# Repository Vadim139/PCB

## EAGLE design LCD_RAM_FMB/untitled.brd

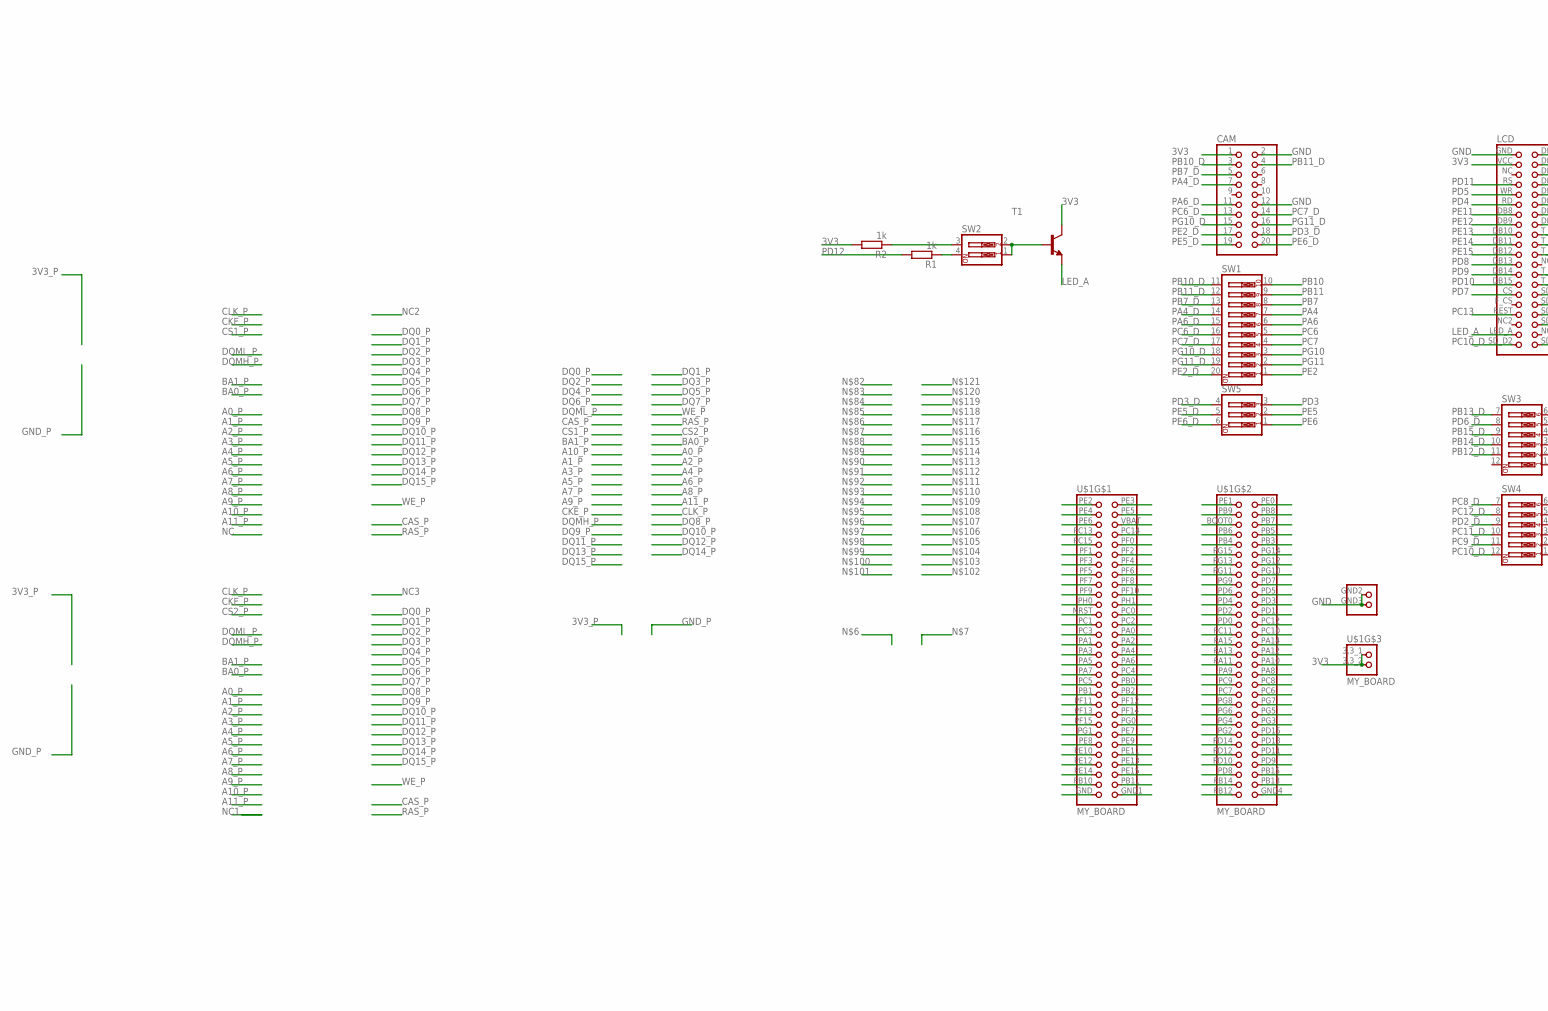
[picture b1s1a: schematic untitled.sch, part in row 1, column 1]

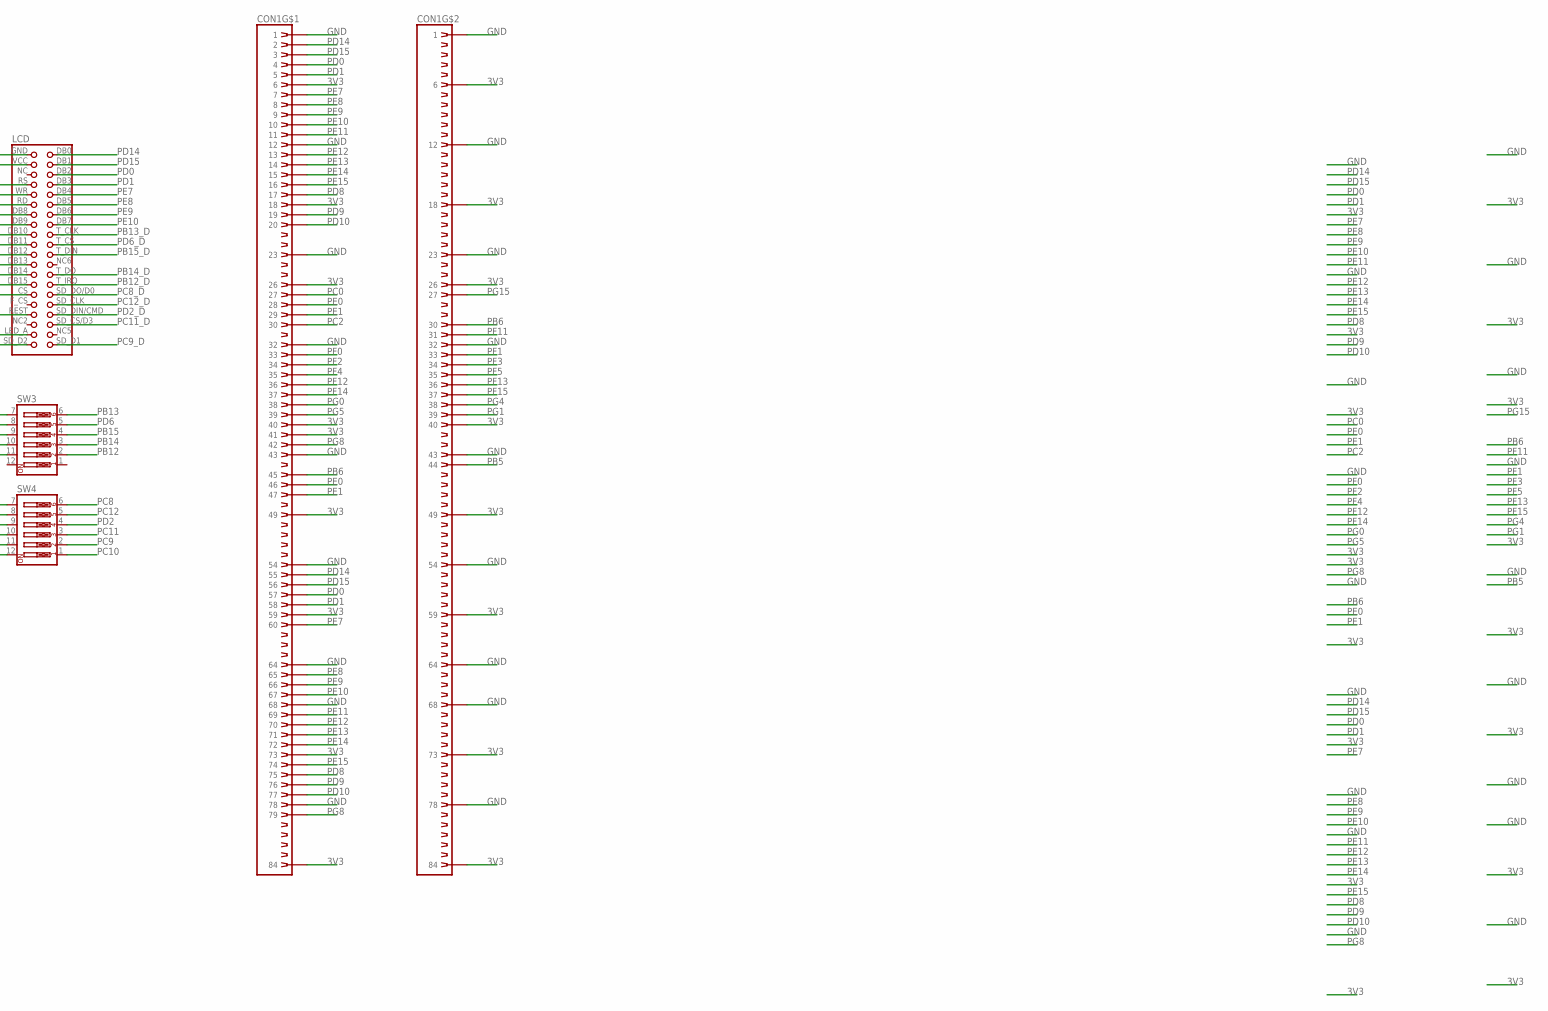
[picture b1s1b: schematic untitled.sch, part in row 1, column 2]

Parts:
CAM: PINHD-2X10; 2X10
CON1: DIMM168; 390052-4
LCD: LCD320QVBLCD320QVB; 2X20
R1, R2: 1k; 0204/5
SW1: SW_DIP-10; EDG-10
SW2: SW_DIP-2; EDG-02
SW3, SW4: SW_DIP-6; EDG-06
SW5: SW_DIP-3; EDG-03
T1: BC337-NPN-TO92-CBE; TO92-CBE
U$1: MY_BOARD

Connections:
3V3: CAM.1, CON1.6, CON1.18, CON1.26, CON1.40, CON1.41, CON1.49, CON1.59, CON1.73, CON1.84, CON1.90 (6), CON1.102 (18), CON1.110 (26), CON1.124 (40), CON1.133 (49), CON1.143 (59), CON1.157 (73), CON1.168 (84), LCD.VCC (3), R2.2, T1.C, U$1.3,3_1 (1), U$1.3,3_2 (2)
BOOT0: U$1.BOOT0 (5)
GND: CAM.2, CAM.12, CON1.1, CON1.12, CON1.23, CON1.32, CON1.43, CON1.54, CON1.64, CON1.68, CON1.78, CON1.85 (1), CON1.96 (12), CON1.107 (23), CON1.116 (32), CON1.127 (43), CON1.138 (54), CON1.148 (64), CON1.152 (68), CON1.162 (78), LCD.GND (1), U$1.GND (59), U$1.GND1 (60), U$1.GND2 (3), U$1.GND3 (4), U$1.GND4 (60)
LED_A: LCD.LED_A (37), T1.E
unnamed: SW2.1, SW2.2, T1.B
unnamed: R2.1, SW2.3
unnamed: R1.1, SW2.4
NRST: U$1.NRST (23)
PA0: U$1.PA0 (28)
PA1: U$1.PA1 (29)
PA2: U$1.PA2 (30)
PA3: U$1.PA3 (31)
PA4: SW1.7, U$1.PA4 (32)
PA4_D: CAM.7, SW1.14
PA5: U$1.PA5 (33)
PA6: SW1.6, U$1.PA6 (34)
PA6_D: CAM.11, SW1.15
PA7: U$1.PA7 (35)
PA8: U$1.PA8 (36)
PA9: U$1.PA9 (35)
PA10: U$1.PA10 (34)
PA11: U$1.PA11 (33)
PA12: U$1.PA12 (32)
PA13: U$1.PA13 (31)
PA14: U$1.PA14 (30)
PA15: U$1.PA15 (29)
PB0: U$1.PB0 (38)
PB1: U$1.PB1 (39)
PB2: U$1.PB2 (40)
PB3: U$1.PB3 (10)
PB4: U$1.PB4 (9)
PB5: CON1.128 (44), U$1.PB5 (8)
PB6: CON1.45, CON1.114 (30), U$1.PB6 (7)
PB7: SW1.8, U$1.PB7 (6)
PB7_D: CAM.5, SW1.13
PB8: U$1.PB8 (4)
PB9: U$1.PB9 (3)
PB10: SW1.10, U$1.PB10 (57)
PB10_D: CAM.3, SW1.11
PB11: SW1.9, U$1.PB11 (58)
PB11_D: CAM.4, SW1.12
PB12: SW3.2, U$1.PB12 (59)
PB12_D: LCD.T_IRQ (28), SW3.11
PB13: SW3.6, U$1.PB13 (58)
PB13_D: LCD.T_CLK (18), SW3.7
PB14: SW3.3, U$1.PB14 (57)
PB14_D: LCD.T_DO (26), SW3.10
PB15: SW3.4, U$1.PB15 (56)
PB15_D: LCD.T_DIN (22), SW3.9
PC0: CON1.27, U$1.PC0 (24)
PC1: U$1.PC1 (25)
PC2: CON1.30, U$1.PC2 (26)
PC3: U$1.PC3 (27)
PC4: U$1.PC4 (36)
PC5: U$1.PC5 (37)
PC6: SW1.5, U$1.PC6 (40)
PC6_D: CAM.13, SW1.16
PC7: SW1.4, U$1.PC7 (39)
PC7_D: CAM.14, SW1.17
PC8: SW4.6, U$1.PC8 (38)
PC8_D: LCD.SD_DO/D0 (30), SW4.7
PC9: SW4.2, U$1.PC9 (37)
PC9_D: LCD.SD_D1 (40), SW4.11
PC10: SW4.1, U$1.PC10 (28)
PC10_D: LCD.SD_D2 (39), SW4.12
PC11: SW4.3, U$1.PC11 (27)
PC11_D: LCD.SD_CS/D3 (36), SW4.10
PC12: SW4.5, U$1.PC12 (26)
PC12_D: LCD.SD_CLK (32), SW4.8
PC13: LCD.REST (33), U$1.PC13 (7)
PC14: U$1.PC14 (8)
PC15: U$1.PC15 (9)
PD0: CON1.4, CON1.57, LCD.DB2 (6), U$1.PD0 (25)
PD1: CON1.5, CON1.58, LCD.DB3 (8), U$1.PD1 (24)
PD2: SW4.4, U$1.PD2 (23)
PD2_D: LCD.SD_DIN/CMD (34), SW4.9
PD3: SW5.3, U$1.PD3 (22)
PD3_D: CAM.18, SW5.4
PD4: LCD.RD (11), U$1.PD4 (21)
PD5: LCD.WR (9), U$1.PD5 (20)
PD6: SW3.5, U$1.PD6 (19)
PD6_D: LCD.T_CS (20), SW3.8
PD7: LCD.CS (29), U$1.PD7 (18)
PD8: CON1.17, CON1.75, LCD.DB13 (23), U$1.PD8 (55)
PD9: CON1.19, CON1.76, LCD.DB14 (25), U$1.PD9 (54)
PD10: CON1.20, CON1.77, LCD.DB15 (27), U$1.PD10 (53)
PD11: LCD.RS (7), U$1.PD11 (52)
PD12: R1.2, U$1.PD12 (51)
PD13: U$1.PD13 (50)
PD14: CON1.2, CON1.55, LCD.DB0 (2), U$1.PD14 (49)
PD15: CON1.3, CON1.56, LCD.DB1 (4), U$1.PD15 (48)
PE0: CON1.28, CON1.46, U$1.PE0 (2)
PE1: CON1.29, CON1.47, U$1.PE1 (1)
PE2: SW1.1, U$1.PE2 (1)
PE2_D: CAM.17, SW1.20
PE3: U$1.PE3 (2)
PE4: U$1.PE4 (3)
PE5: SW5.2, U$1.PE5 (4)
PE5_D: CAM.19, SW5.5
PE6: SW5.1, U$1.PE6 (5)
PE6_D: CAM.20, SW5.6
PE7: CON1.7, CON1.60, LCD.DB4 (10), U$1.PE7 (48)
PE8: CON1.8, CON1.65, LCD.DB5 (12), U$1.PE8 (49)
PE9: CON1.9, CON1.66, LCD.DB6 (14), U$1.PE9 (50)
PE10: CON1.10, CON1.67, LCD.DB7 (16), U$1.PE10 (51)
PE11: CON1.11, CON1.69, LCD.DB8 (13), U$1.PE11 (52)
PE12: CON1.13, CON1.70, LCD.DB9 (15), U$1.PE12 (53)
PE13: CON1.14, CON1.71, LCD.DB10 (17), U$1.PE13 (54)
PE14: CON1.15, CON1.72, LCD.DB11 (19), U$1.PE14 (55)
PE15: CON1.16, CON1.74, LCD.DB12 (21), U$1.PE15 (56)
PF0: CON1.33, U$1.PF0 (10)
PF1: CON1.117 (33), U$1.PF1 (11)
PF2: CON1.34, U$1.PF2 (12)
PF3: CON1.118 (34), U$1.PF3 (13)
PF4: CON1.35, U$1.PF4 (14)
PF5: CON1.119 (35), U$1.PF5 (15)
PF6: U$1.PF6 (16)
PF7: U$1.PF7 (17)
PF8: U$1.PF8 (18)
PF9: U$1.PF9 (19)
PF10: U$1.PF10 (20)
PF11: CON1.115 (31), U$1.PF11 (41)
PF12: CON1.36, U$1.PF12 (42)
PF13: CON1.120 (36), U$1.PF13 (43)
PF14: CON1.37, U$1.PF14 (44)
PF15: CON1.121 (37), U$1.PF15 (45)
PG0: CON1.38, U$1.PG0 (46)
PG1: CON1.123 (39), U$1.PG1 (47)
PG2: U$1.PG2 (47)
PG3: U$1.PG3 (46)
PG4: CON1.122 (38), U$1.PG4 (45)
PG5: CON1.39, U$1.PG5 (44)
PG6: U$1.PG6 (43)
PG7: U$1.PG7 (42)
PG8: CON1.42, CON1.79, U$1.PG8 (41)
PG9: U$1.PG9 (17)
PG10: SW1.3, U$1.PG10 (16)
PG10_D: CAM.15, SW1.18
PG11: SW1.2, U$1.PG11 (15)
PG11_D: CAM.16, SW1.19
PG12: U$1.PG12 (14)
PG13: U$1.PG13 (13)
PG14: U$1.PG14 (12)
PG15: CON1.111 (27), U$1.PG15 (11)
PH0: U$1.PH0 (21)
PH1: U$1.PH1 (22)
VBAT: U$1.VBAT (6)

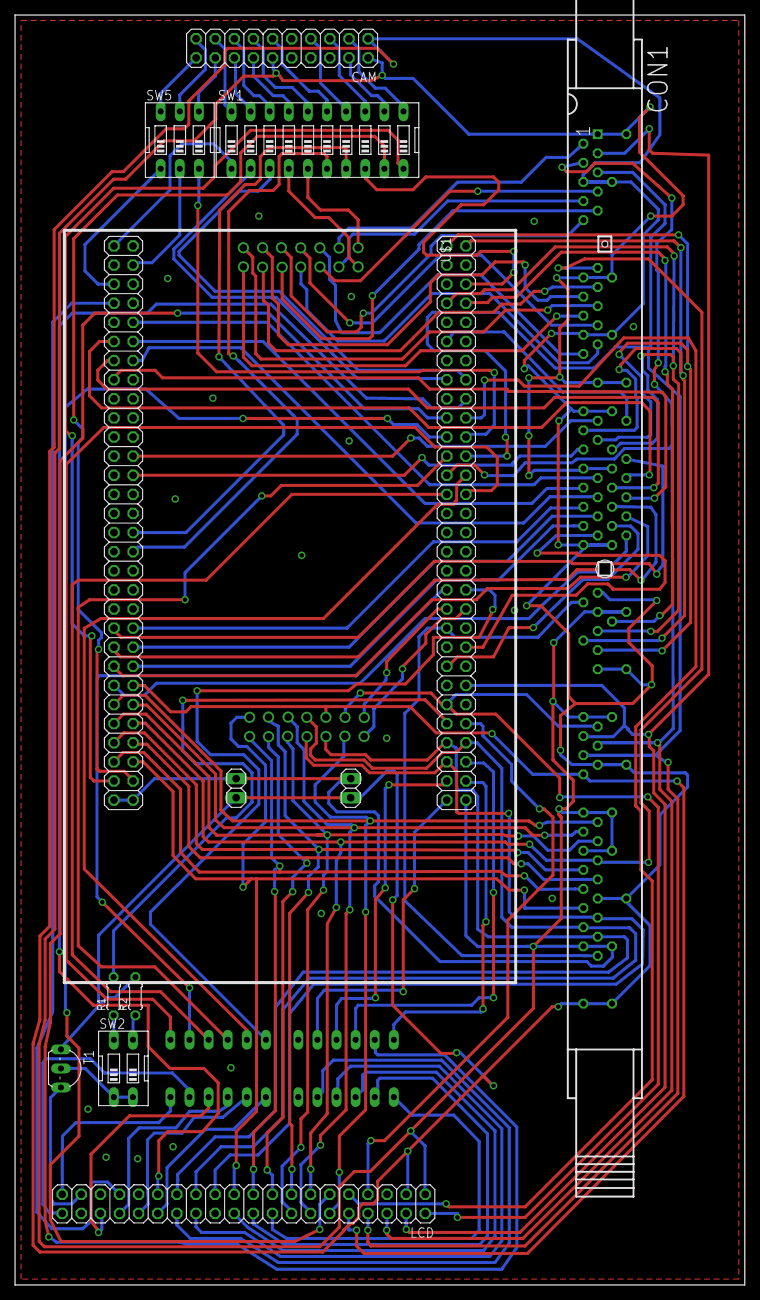
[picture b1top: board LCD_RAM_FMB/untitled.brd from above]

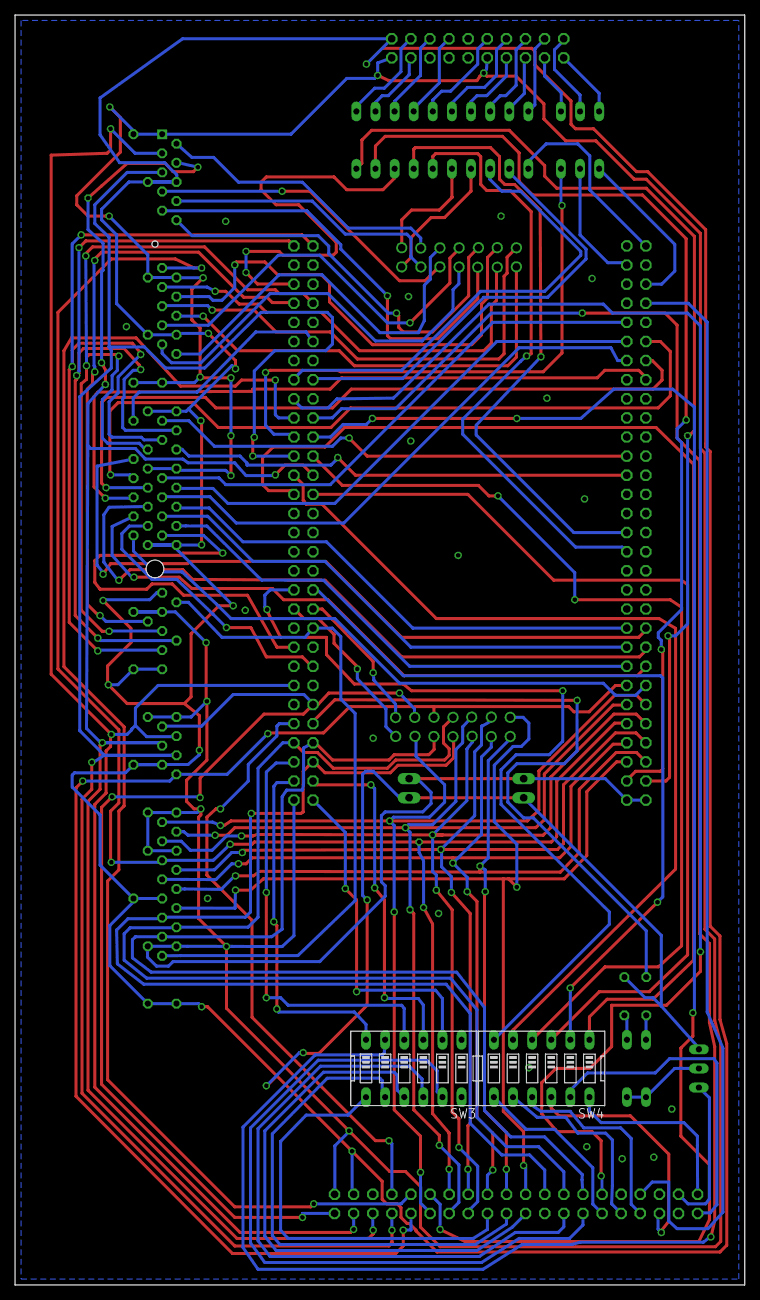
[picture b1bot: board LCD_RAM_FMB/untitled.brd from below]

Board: 2 copper layers, 97.0 x 168.8 mm, 12 parts (2 on the bottom side), 99 nets.

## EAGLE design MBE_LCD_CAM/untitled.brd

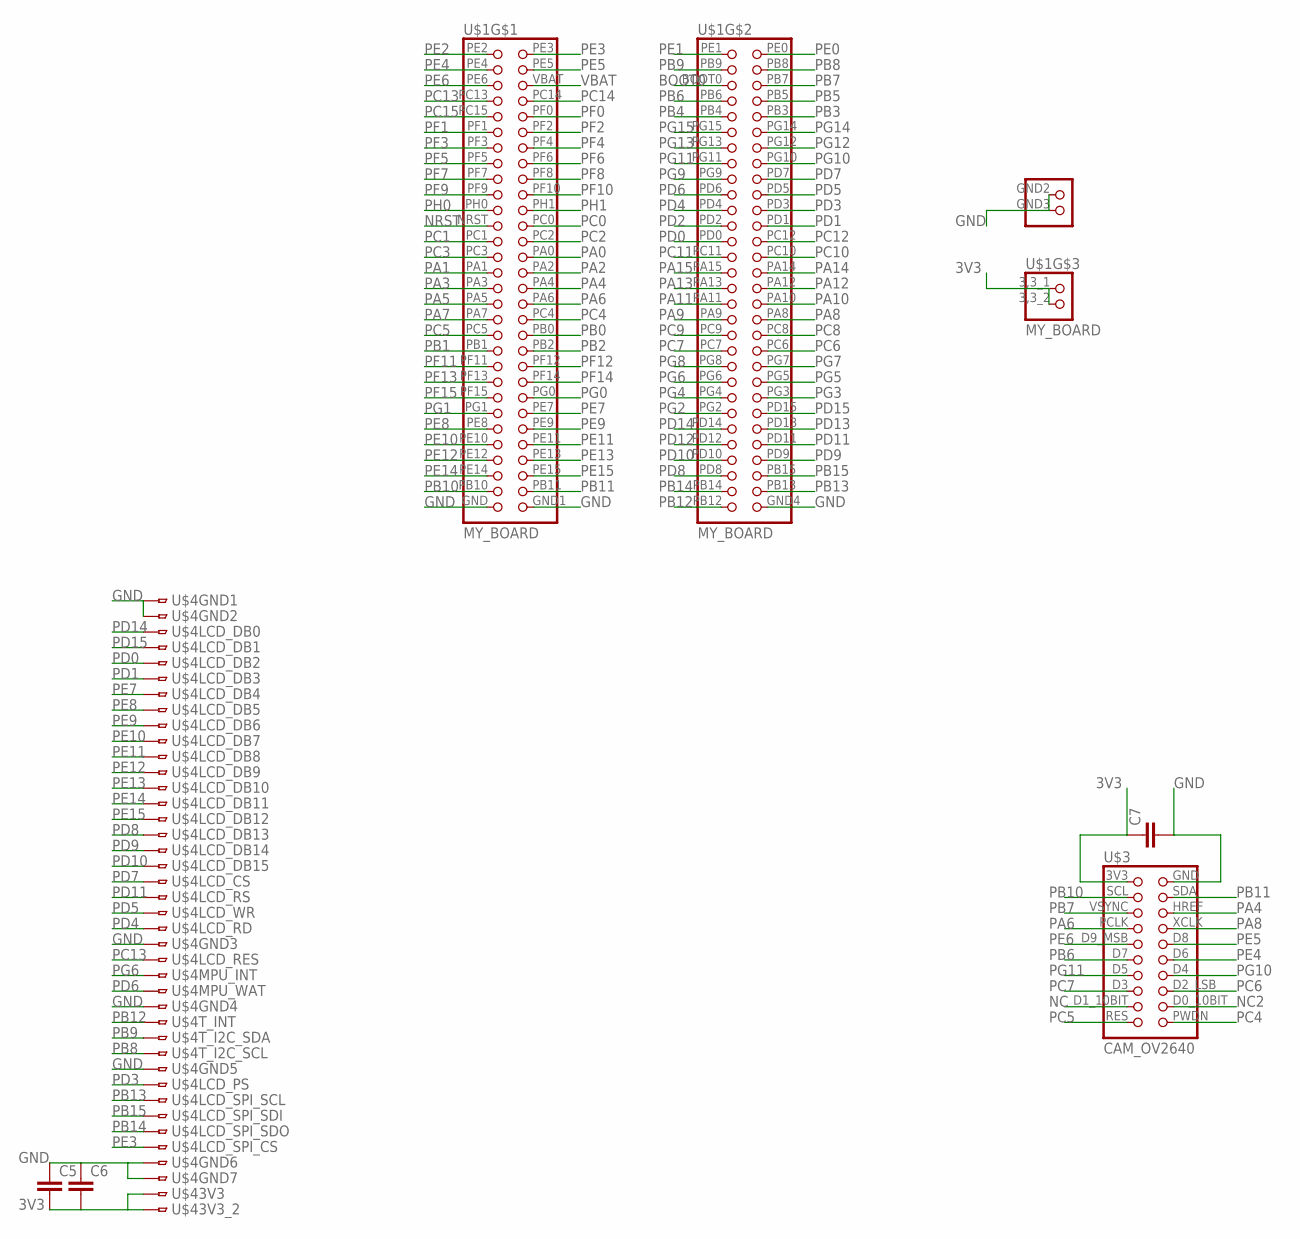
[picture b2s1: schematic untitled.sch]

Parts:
C5, C6, C7: C-EUC1206; C1206
U$1: MY_BOARD
U$3: CAM_OV2640
U$4: LCD800TFT; FH12-40S-0.5SH

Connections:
3V3: C5.2, C6.2, C7.1, U$1.3,3_1 (1), U$1.3,3_2 (2), U$3.3V3, U$4.39, U$4.40
BOOT0: U$1.BOOT0 (5)
GND: C5.1, C6.1, C7.2, U$1.GND (59), U$1.GND1 (60), U$1.GND2 (3), U$1.GND3 (4), U$1.GND4 (60), U$3.GND, U$4.1, U$4.2, U$4.23, U$4.27, U$4.31, U$4.37, U$4.38
NC: U$3.D1_10BIT
NC2: U$3.D0_10BIT
NRST: U$1.NRST (23)
PA0: U$1.PA0 (28)
PA1: U$1.PA1 (29)
PA2: U$1.PA2 (30)
PA3: U$1.PA3 (31)
PA4: U$1.PA4 (32), U$3.HREF
PA5: U$1.PA5 (33)
PA6: U$1.PA6 (34), U$3.PCLK
PA7: U$1.PA7 (35)
PA8: U$1.PA8 (36), U$3.XCLK
PA9: U$1.PA9 (35)
PA10: U$1.PA10 (34)
PA11: U$1.PA11 (33)
PA12: U$1.PA12 (32)
PA13: U$1.PA13 (31)
PA14: U$1.PA14 (30)
PA15: U$1.PA15 (29)
PB0: U$1.PB0 (38)
PB1: U$1.PB1 (39)
PB2: U$1.PB2 (40)
PB3: U$1.PB3 (10)
PB4: U$1.PB4 (9)
PB5: U$1.PB5 (8)
PB6: U$1.PB6 (7), U$3.D7
PB7: U$1.PB7 (6), U$3.VSYNC
PB8: U$1.PB8 (4), U$4.30
PB9: U$1.PB9 (3), U$4.29
PB10: U$1.PB10 (57), U$3.SCL
PB11: U$1.PB11 (58), U$3.SDA
PB12: U$1.PB12 (59), U$4.28
PB13: U$1.PB13 (58), U$4.33
PB14: U$1.PB14 (57), U$4.35
PB15: U$1.PB15 (56), U$4.34
PC0: U$1.PC0 (24)
PC1: U$1.PC1 (25)
PC2: U$1.PC2 (26)
PC3: U$1.PC3 (27)
PC4: U$1.PC4 (36), U$3.PWDN
PC5: U$1.PC5 (37), U$3.RES
PC6: U$1.PC6 (40), U$3.D2_LSB
PC7: U$1.PC7 (39), U$3.D3
PC8: U$1.PC8 (38)
PC9: U$1.PC9 (37)
PC10: U$1.PC10 (28)
PC11: U$1.PC11 (27)
PC12: U$1.PC12 (26)
PC13: U$1.PC13 (7), U$4.24
PC14: U$1.PC14 (8)
PC15: U$1.PC15 (9)
PD0: U$1.PD0 (25), U$4.5
PD1: U$1.PD1 (24), U$4.6
PD2: U$1.PD2 (23)
PD3: U$1.PD3 (22), U$4.32
PD4: U$1.PD4 (21), U$4.22
PD5: U$1.PD5 (20), U$4.21
PD6: U$1.PD6 (19), U$4.26
PD7: U$1.PD7 (18), U$4.19
PD8: U$1.PD8 (55), U$4.16
PD9: U$1.PD9 (54), U$4.17
PD10: U$1.PD10 (53), U$4.18
PD11: U$1.PD11 (52), U$4.20
PD12: U$1.PD12 (51)
PD13: U$1.PD13 (50)
PD14: U$1.PD14 (49), U$4.3
PD15: U$1.PD15 (48), U$4.4
PE0: U$1.PE0 (2)
PE1: U$1.PE1 (1)
PE2: U$1.PE2 (1)
PE3: U$1.PE3 (2), U$4.36
PE4: U$1.PE4 (3), U$3.D6
PE5: U$1.PE5 (4), U$3.D8
PE6: U$1.PE6 (5), U$3.D9_MSB
PE7: U$1.PE7 (48), U$4.7
PE8: U$1.PE8 (49), U$4.8
PE9: U$1.PE9 (50), U$4.9
PE10: U$1.PE10 (51), U$4.10
PE11: U$1.PE11 (52), U$4.11
PE12: U$1.PE12 (53), U$4.12
PE13: U$1.PE13 (54), U$4.13
PE14: U$1.PE14 (55), U$4.14
PE15: U$1.PE15 (56), U$4.15
PF0: U$1.PF0 (10)
PF1: U$1.PF1 (11)
PF2: U$1.PF2 (12)
PF3: U$1.PF3 (13)
PF4: U$1.PF4 (14)
PF5: U$1.PF5 (15)
PF6: U$1.PF6 (16)
PF7: U$1.PF7 (17)
PF8: U$1.PF8 (18)
PF9: U$1.PF9 (19)
PF10: U$1.PF10 (20)
PF11: U$1.PF11 (41)
PF12: U$1.PF12 (42)
PF13: U$1.PF13 (43)
PF14: U$1.PF14 (44)
PF15: U$1.PF15 (45)
PG0: U$1.PG0 (46)
PG1: U$1.PG1 (47)
PG2: U$1.PG2 (47)
PG3: U$1.PG3 (46)
PG4: U$1.PG4 (45)
PG5: U$1.PG5 (44)
PG6: U$1.PG6 (43), U$4.25
PG7: U$1.PG7 (42)
PG8: U$1.PG8 (41)
PG9: U$1.PG9 (17)
PG10: U$1.PG10 (16), U$3.D4
PG11: U$1.PG11 (15), U$3.D5
PG12: U$1.PG12 (14)
PG13: U$1.PG13 (13)
PG14: U$1.PG14 (12)
PG15: U$1.PG15 (11)
PH0: U$1.PH0 (21)
PH1: U$1.PH1 (22)
VBAT: U$1.VBAT (6)

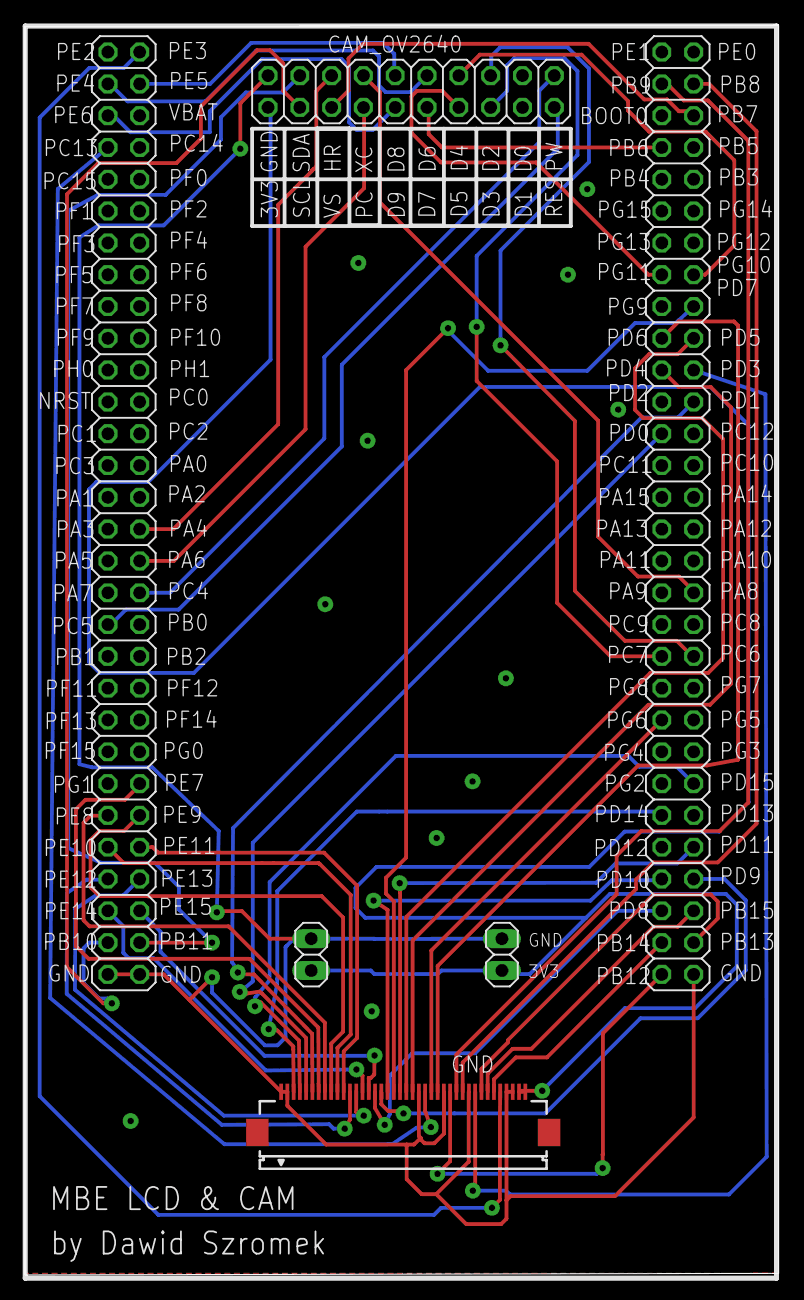
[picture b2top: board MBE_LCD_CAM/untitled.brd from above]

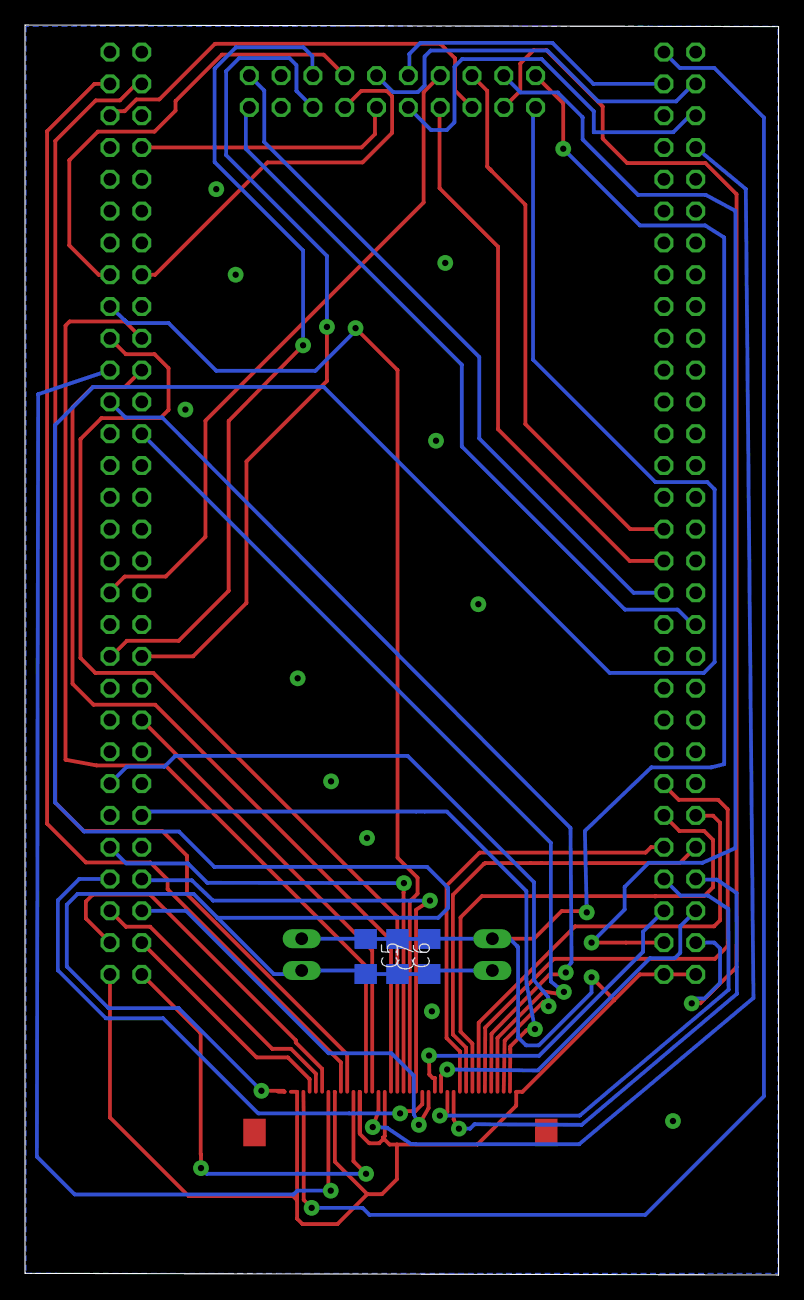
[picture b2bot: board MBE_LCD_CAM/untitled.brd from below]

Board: 2 copper layers, 60.2 x 99.8 mm, 6 parts (3 on the bottom side), 49 nets.

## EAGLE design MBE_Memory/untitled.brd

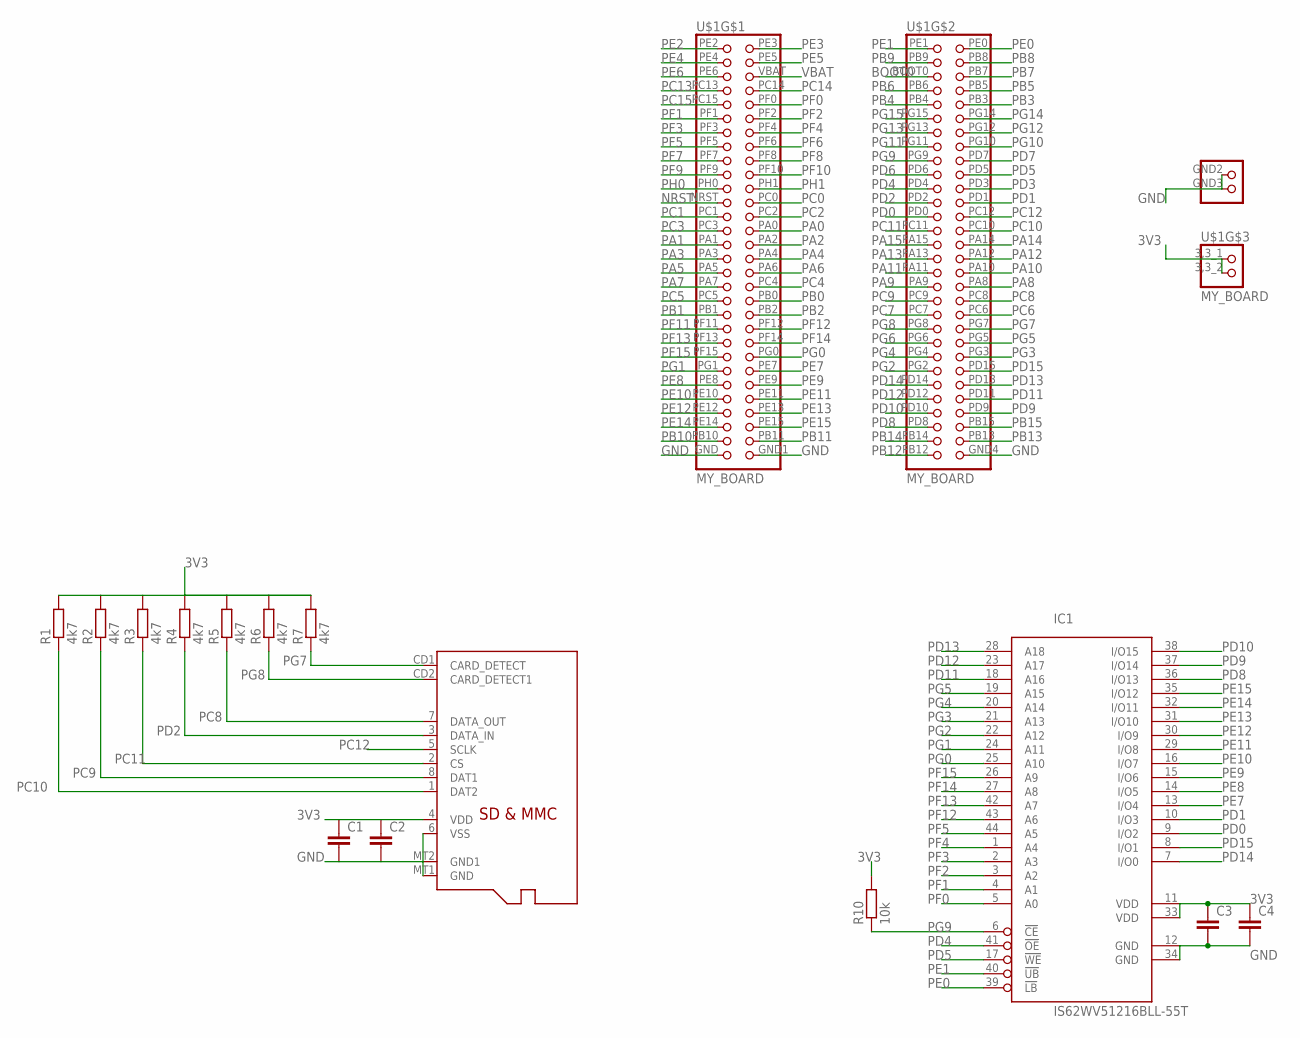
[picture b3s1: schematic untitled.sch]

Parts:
C1, C2, C3, C4: C-EUC1206; C1206
IC1: IS62WV51216BLL-55T; TSOP-II-44
R1, R2, R3, R4, R5, R6, R7: 4k7; R1206
R10: 10k; R1206
U$1: MY_BOARD
U$5: MICROSD

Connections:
3V3: C1.1, C2.1, C3.1, C4.1, IC1.11 (VDD), IC1.33 (VDD), R1.2, R2.2, R3.2, R4.2, R5.2, R6.2, R7.2, R10.2, U$1.3,3_1 (1), U$1.3,3_2 (2), U$5.4 (VDD)
BOOT0: U$1.BOOT0 (5)
GND: C1.2, C2.2, C3.2, C4.2, IC1.12 (GND), IC1.34 (GND), U$1.GND (59), U$1.GND1 (60), U$1.GND2 (3), U$1.GND3 (4), U$1.GND4 (60), U$5.6 (VSS), U$5.MT1 (GND), U$5.MT2 (GND1)
NRST: U$1.NRST (23)
PA0: U$1.PA0 (28)
PA1: U$1.PA1 (29)
PA2: U$1.PA2 (30)
PA3: U$1.PA3 (31)
PA4: U$1.PA4 (32)
PA5: U$1.PA5 (33)
PA6: U$1.PA6 (34)
PA7: U$1.PA7 (35)
PA8: U$1.PA8 (36)
PA9: U$1.PA9 (35)
PA10: U$1.PA10 (34)
PA11: U$1.PA11 (33)
PA12: U$1.PA12 (32)
PA13: U$1.PA13 (31)
PA14: U$1.PA14 (30)
PA15: U$1.PA15 (29)
PB0: U$1.PB0 (38)
PB1: U$1.PB1 (39)
PB2: U$1.PB2 (40)
PB3: U$1.PB3 (10)
PB4: U$1.PB4 (9)
PB5: U$1.PB5 (8)
PB6: U$1.PB6 (7)
PB7: U$1.PB7 (6)
PB8: U$1.PB8 (4)
PB9: U$1.PB9 (3)
PB10: U$1.PB10 (57)
PB11: U$1.PB11 (58)
PB12: U$1.PB12 (59)
PB13: U$1.PB13 (58)
PB14: U$1.PB14 (57)
PB15: U$1.PB15 (56)
PC0: U$1.PC0 (24)
PC1: U$1.PC1 (25)
PC2: U$1.PC2 (26)
PC3: U$1.PC3 (27)
PC4: U$1.PC4 (36)
PC5: U$1.PC5 (37)
PC6: U$1.PC6 (40)
PC7: U$1.PC7 (39)
PC8: R5.1, U$1.PC8 (38), U$5.7 (DATA_OUT)
PC9: R2.1, U$1.PC9 (37), U$5.8 (DAT1)
PC10: R1.1, U$1.PC10 (28), U$5.1 (DAT2)
PC11: R3.1, U$1.PC11 (27), U$5.2 (CS)
PC12: U$1.PC12 (26), U$5.5 (SCLK)
PC13: U$1.PC13 (7)
PC14: U$1.PC14 (8)
PC15: U$1.PC15 (9)
PD0: IC1.9 (I/O2), U$1.PD0 (25)
PD1: IC1.10 (I/O3), U$1.PD1 (24)
PD2: R4.1, U$1.PD2 (23), U$5.3 (DATA_IN)
PD3: U$1.PD3 (22)
PD4: IC1.41 (!OE), U$1.PD4 (21)
PD5: IC1.17 (!WE), U$1.PD5 (20)
PD6: U$1.PD6 (19)
PD7: U$1.PD7 (18)
PD8: IC1.36 (I/O13), U$1.PD8 (55)
PD9: IC1.37 (I/O14), U$1.PD9 (54)
PD10: IC1.38 (I/O15), U$1.PD10 (53)
PD11: IC1.18 (A16), U$1.PD11 (52)
PD12: IC1.23 (A17), U$1.PD12 (51)
PD13: IC1.28 (A18), U$1.PD13 (50)
PD14: IC1.7 (I/O0), U$1.PD14 (49)
PD15: IC1.8 (I/O1), U$1.PD15 (48)
PE0: IC1.39 (!LB), U$1.PE0 (2)
PE1: IC1.40 (!UB), U$1.PE1 (1)
PE2: U$1.PE2 (1)
PE3: U$1.PE3 (2)
PE4: U$1.PE4 (3)
PE5: U$1.PE5 (4)
PE6: U$1.PE6 (5)
PE7: IC1.13 (I/O4), U$1.PE7 (48)
PE8: IC1.14 (I/O5), U$1.PE8 (49)
PE9: IC1.15 (I/O6), U$1.PE9 (50)
PE10: IC1.16 (I/O7), U$1.PE10 (51)
PE11: IC1.29 (I/O8), U$1.PE11 (52)
PE12: IC1.30 (I/O9), U$1.PE12 (53)
PE13: IC1.31 (I/O10), U$1.PE13 (54)
PE14: IC1.32 (I/O11), U$1.PE14 (55)
PE15: IC1.35 (I/O12), U$1.PE15 (56)
PF0: IC1.5 (A0), U$1.PF0 (10)
PF1: IC1.4 (A1), U$1.PF1 (11)
PF2: IC1.3 (A2), U$1.PF2 (12)
PF3: IC1.2 (A3), U$1.PF3 (13)
PF4: IC1.1 (A4), U$1.PF4 (14)
PF5: IC1.44 (A5), U$1.PF5 (15)
PF6: U$1.PF6 (16)
PF7: U$1.PF7 (17)
PF8: U$1.PF8 (18)
PF9: U$1.PF9 (19)
PF10: U$1.PF10 (20)
PF11: U$1.PF11 (41)
PF12: IC1.43 (A6), U$1.PF12 (42)
PF13: IC1.42 (A7), U$1.PF13 (43)
PF14: IC1.27 (A8), U$1.PF14 (44)
PF15: IC1.26 (A9), U$1.PF15 (45)
PG0: IC1.25 (A10), U$1.PG0 (46)
PG1: IC1.24 (A11), U$1.PG1 (47)
PG2: IC1.22 (A12), U$1.PG2 (47)
PG3: IC1.21 (A13), U$1.PG3 (46)
PG4: IC1.20 (A14), U$1.PG4 (45)
PG5: IC1.19 (A15), U$1.PG5 (44)
PG6: U$1.PG6 (43)
PG7: R7.1, U$1.PG7 (42), U$5.CD1 (CARD_DETECT)
PG8: R6.1, U$1.PG8 (41), U$5.CD2 (CARD_DETECT1)
PG9: IC1.6 (!CE), R10.1, U$1.PG9 (17)
PG10: U$1.PG10 (16)
PG11: U$1.PG11 (15)
PG12: U$1.PG12 (14)
PG13: U$1.PG13 (13)
PG14: U$1.PG14 (12)
PG15: U$1.PG15 (11)
PH0: U$1.PH0 (21)
PH1: U$1.PH1 (22)
VBAT: U$1.VBAT (6)

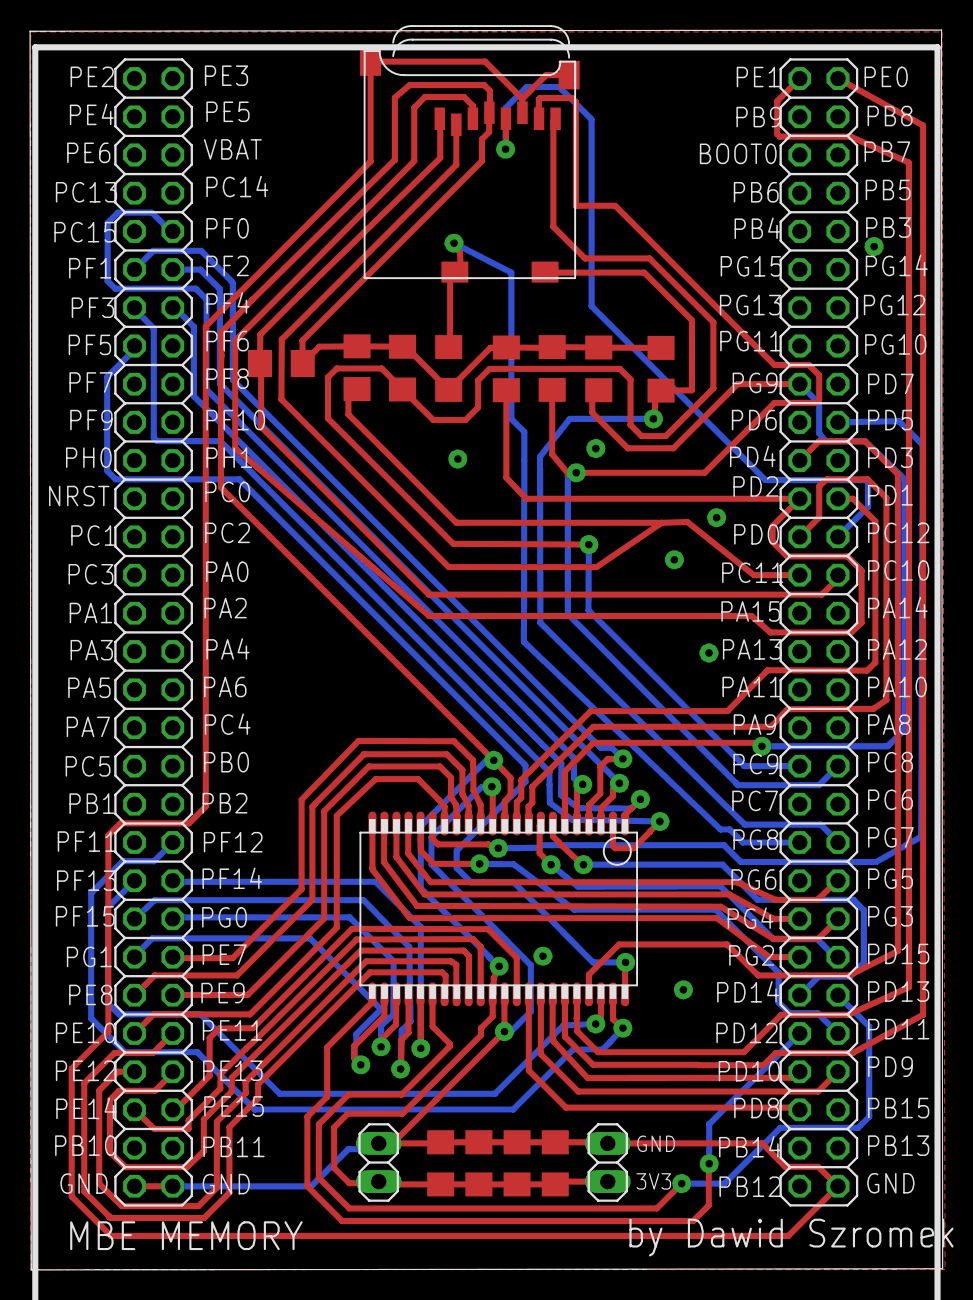
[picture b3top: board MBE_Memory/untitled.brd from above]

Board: 2 copper layers, 60.7 x 82.4 mm, 15 parts (0 on the bottom side), 50 nets.

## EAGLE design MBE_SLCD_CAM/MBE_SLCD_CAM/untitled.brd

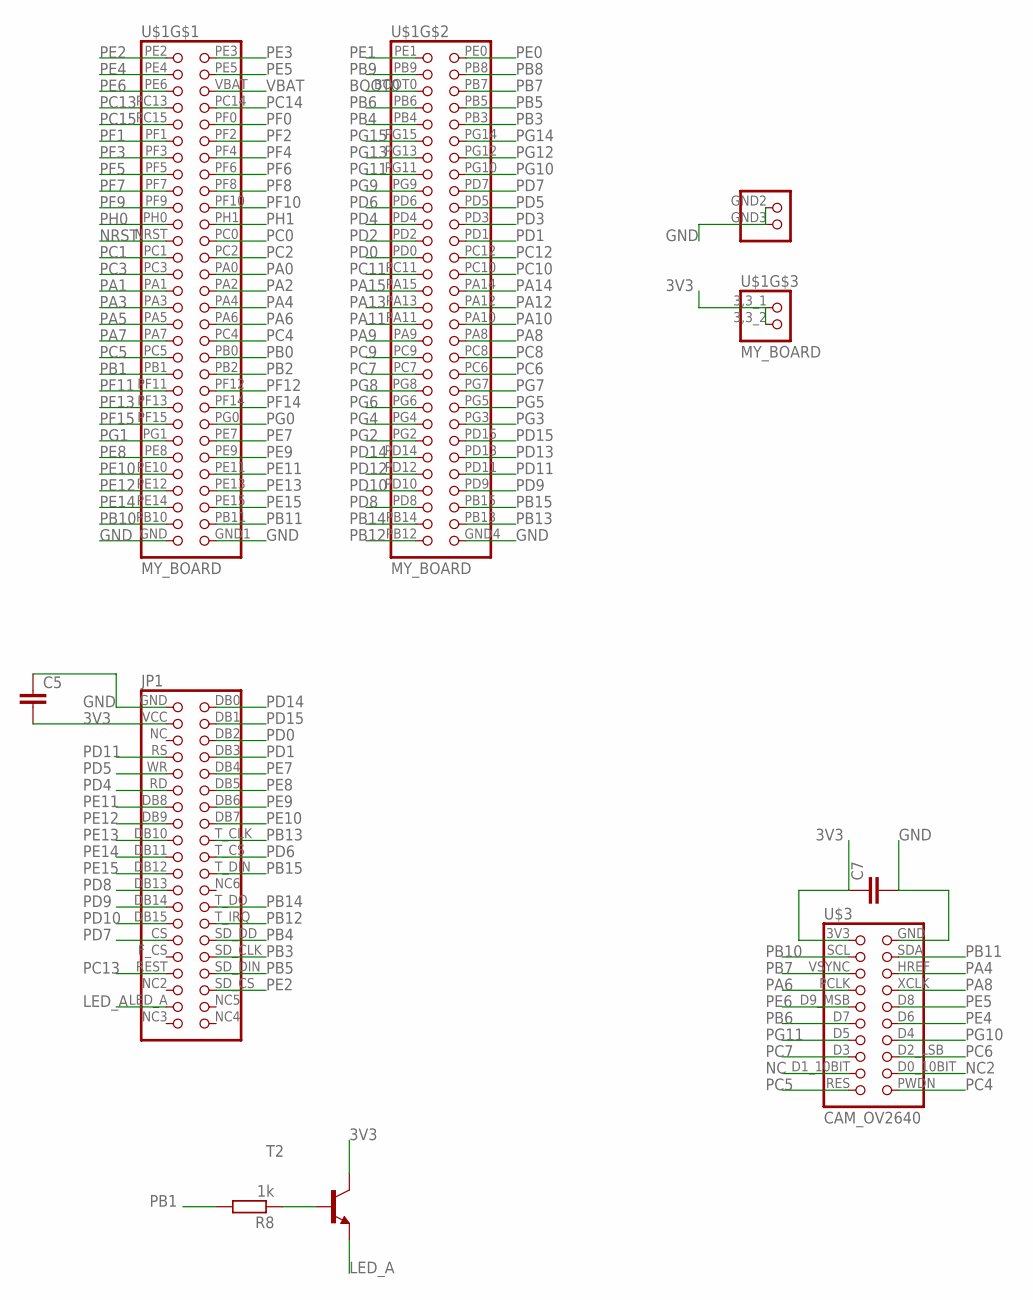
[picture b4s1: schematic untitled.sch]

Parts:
C5, C7: C-EUC1206; C1206
JP1: LCD320QVBLCD320QVB; 2X20
R8: 1k; R1206
T2: BC817-16-NPN-SOT23-BEC; SOT23-BEC
U$1: MY_BOARD
U$3: CAM_OV2640

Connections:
3V3: C5.2, C7.1, JP1.VCC (3), T2.C, U$1.3,3_1 (1), U$1.3,3_2 (2), U$3.3V3
BOOT0: U$1.BOOT0 (5)
GND: C5.1, C7.2, JP1.GND (1), U$1.GND (59), U$1.GND1 (60), U$1.GND2 (3), U$1.GND3 (4), U$1.GND4 (60), U$3.GND
LED_A: JP1.LED_A (37), T2.E
unnamed: R8.1, T2.B
NC: U$3.D1_10BIT
NC2: U$3.D0_10BIT
NRST: U$1.NRST (23)
PA0: U$1.PA0 (28)
PA1: U$1.PA1 (29)
PA2: U$1.PA2 (30)
PA3: U$1.PA3 (31)
PA4: U$1.PA4 (32), U$3.HREF
PA5: U$1.PA5 (33)
PA6: U$1.PA6 (34), U$3.PCLK
PA7: U$1.PA7 (35)
PA8: U$1.PA8 (36), U$3.XCLK
PA9: U$1.PA9 (35)
PA10: U$1.PA10 (34)
PA11: U$1.PA11 (33)
PA12: U$1.PA12 (32)
PA13: U$1.PA13 (31)
PA14: U$1.PA14 (30)
PA15: U$1.PA15 (29)
PB0: U$1.PB0 (38)
PB1: R8.2, U$1.PB1 (39)
PB2: U$1.PB2 (40)
PB3: JP1.SD_CLK (32), U$1.PB3 (10)
PB4: JP1.SD_DD (30), U$1.PB4 (9)
PB5: JP1.SD_DIN (34), U$1.PB5 (8)
PB6: U$1.PB6 (7), U$3.D7
PB7: U$1.PB7 (6), U$3.VSYNC
PB8: U$1.PB8 (4)
PB9: U$1.PB9 (3)
PB10: U$1.PB10 (57), U$3.SCL
PB11: U$1.PB11 (58), U$3.SDA
PB12: JP1.T_IRQ (28), U$1.PB12 (59)
PB13: JP1.T_CLK (18), U$1.PB13 (58)
PB14: JP1.T_DO (26), U$1.PB14 (57)
PB15: JP1.T_DIN (22), U$1.PB15 (56)
PC0: U$1.PC0 (24)
PC1: U$1.PC1 (25)
PC2: U$1.PC2 (26)
PC3: U$1.PC3 (27)
PC4: U$1.PC4 (36), U$3.PWDN
PC5: U$1.PC5 (37), U$3.RES
PC6: U$1.PC6 (40), U$3.D2_LSB
PC7: U$1.PC7 (39), U$3.D3
PC8: U$1.PC8 (38)
PC9: U$1.PC9 (37)
PC10: U$1.PC10 (28)
PC11: U$1.PC11 (27)
PC12: U$1.PC12 (26)
PC13: JP1.REST (33), U$1.PC13 (7)
PC14: U$1.PC14 (8)
PC15: U$1.PC15 (9)
PD0: JP1.DB2 (6), U$1.PD0 (25)
PD1: JP1.DB3 (8), U$1.PD1 (24)
PD2: U$1.PD2 (23)
PD3: U$1.PD3 (22)
PD4: JP1.RD (11), U$1.PD4 (21)
PD5: JP1.WR (9), U$1.PD5 (20)
PD6: JP1.T_CS (20), U$1.PD6 (19)
PD7: JP1.CS (29), U$1.PD7 (18)
PD8: JP1.DB13 (23), U$1.PD8 (55)
PD9: JP1.DB14 (25), U$1.PD9 (54)
PD10: JP1.DB15 (27), U$1.PD10 (53)
PD11: JP1.RS (7), U$1.PD11 (52)
PD12: U$1.PD12 (51)
PD13: U$1.PD13 (50)
PD14: JP1.DB0 (2), U$1.PD14 (49)
PD15: JP1.DB1 (4), U$1.PD15 (48)
PE0: U$1.PE0 (2)
PE1: U$1.PE1 (1)
PE2: JP1.SD_CS (36), U$1.PE2 (1)
PE3: U$1.PE3 (2)
PE4: U$1.PE4 (3), U$3.D6
PE5: U$1.PE5 (4), U$3.D8
PE6: U$1.PE6 (5), U$3.D9_MSB
PE7: JP1.DB4 (10), U$1.PE7 (48)
PE8: JP1.DB5 (12), U$1.PE8 (49)
PE9: JP1.DB6 (14), U$1.PE9 (50)
PE10: JP1.DB7 (16), U$1.PE10 (51)
PE11: JP1.DB8 (13), U$1.PE11 (52)
PE12: JP1.DB9 (15), U$1.PE12 (53)
PE13: JP1.DB10 (17), U$1.PE13 (54)
PE14: JP1.DB11 (19), U$1.PE14 (55)
PE15: JP1.DB12 (21), U$1.PE15 (56)
PF0: U$1.PF0 (10)
PF1: U$1.PF1 (11)
PF2: U$1.PF2 (12)
PF3: U$1.PF3 (13)
PF4: U$1.PF4 (14)
PF5: U$1.PF5 (15)
PF6: U$1.PF6 (16)
PF7: U$1.PF7 (17)
PF8: U$1.PF8 (18)
PF9: U$1.PF9 (19)
PF10: U$1.PF10 (20)
PF11: U$1.PF11 (41)
PF12: U$1.PF12 (42)
PF13: U$1.PF13 (43)
PF14: U$1.PF14 (44)
PF15: U$1.PF15 (45)
PG0: U$1.PG0 (46)
PG1: U$1.PG1 (47)
PG2: U$1.PG2 (47)
PG3: U$1.PG3 (46)
PG4: U$1.PG4 (45)
PG5: U$1.PG5 (44)
PG6: U$1.PG6 (43)
PG7: U$1.PG7 (42)
PG8: U$1.PG8 (41)
PG9: U$1.PG9 (17)
PG10: U$1.PG10 (16), U$3.D4
PG11: U$1.PG11 (15), U$3.D5
PG12: U$1.PG12 (14)
PG13: U$1.PG13 (13)
PG14: U$1.PG14 (12)
PG15: U$1.PG15 (11)
PH0: U$1.PH0 (21)
PH1: U$1.PH1 (22)
VBAT: U$1.VBAT (6)

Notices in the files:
parts and their libraries:
SparkFun-Electromechanical: Licensing: Creative Commons ShareAlike 4.0 International - https://creativecommons.org/licenses/by-sa/4.0
